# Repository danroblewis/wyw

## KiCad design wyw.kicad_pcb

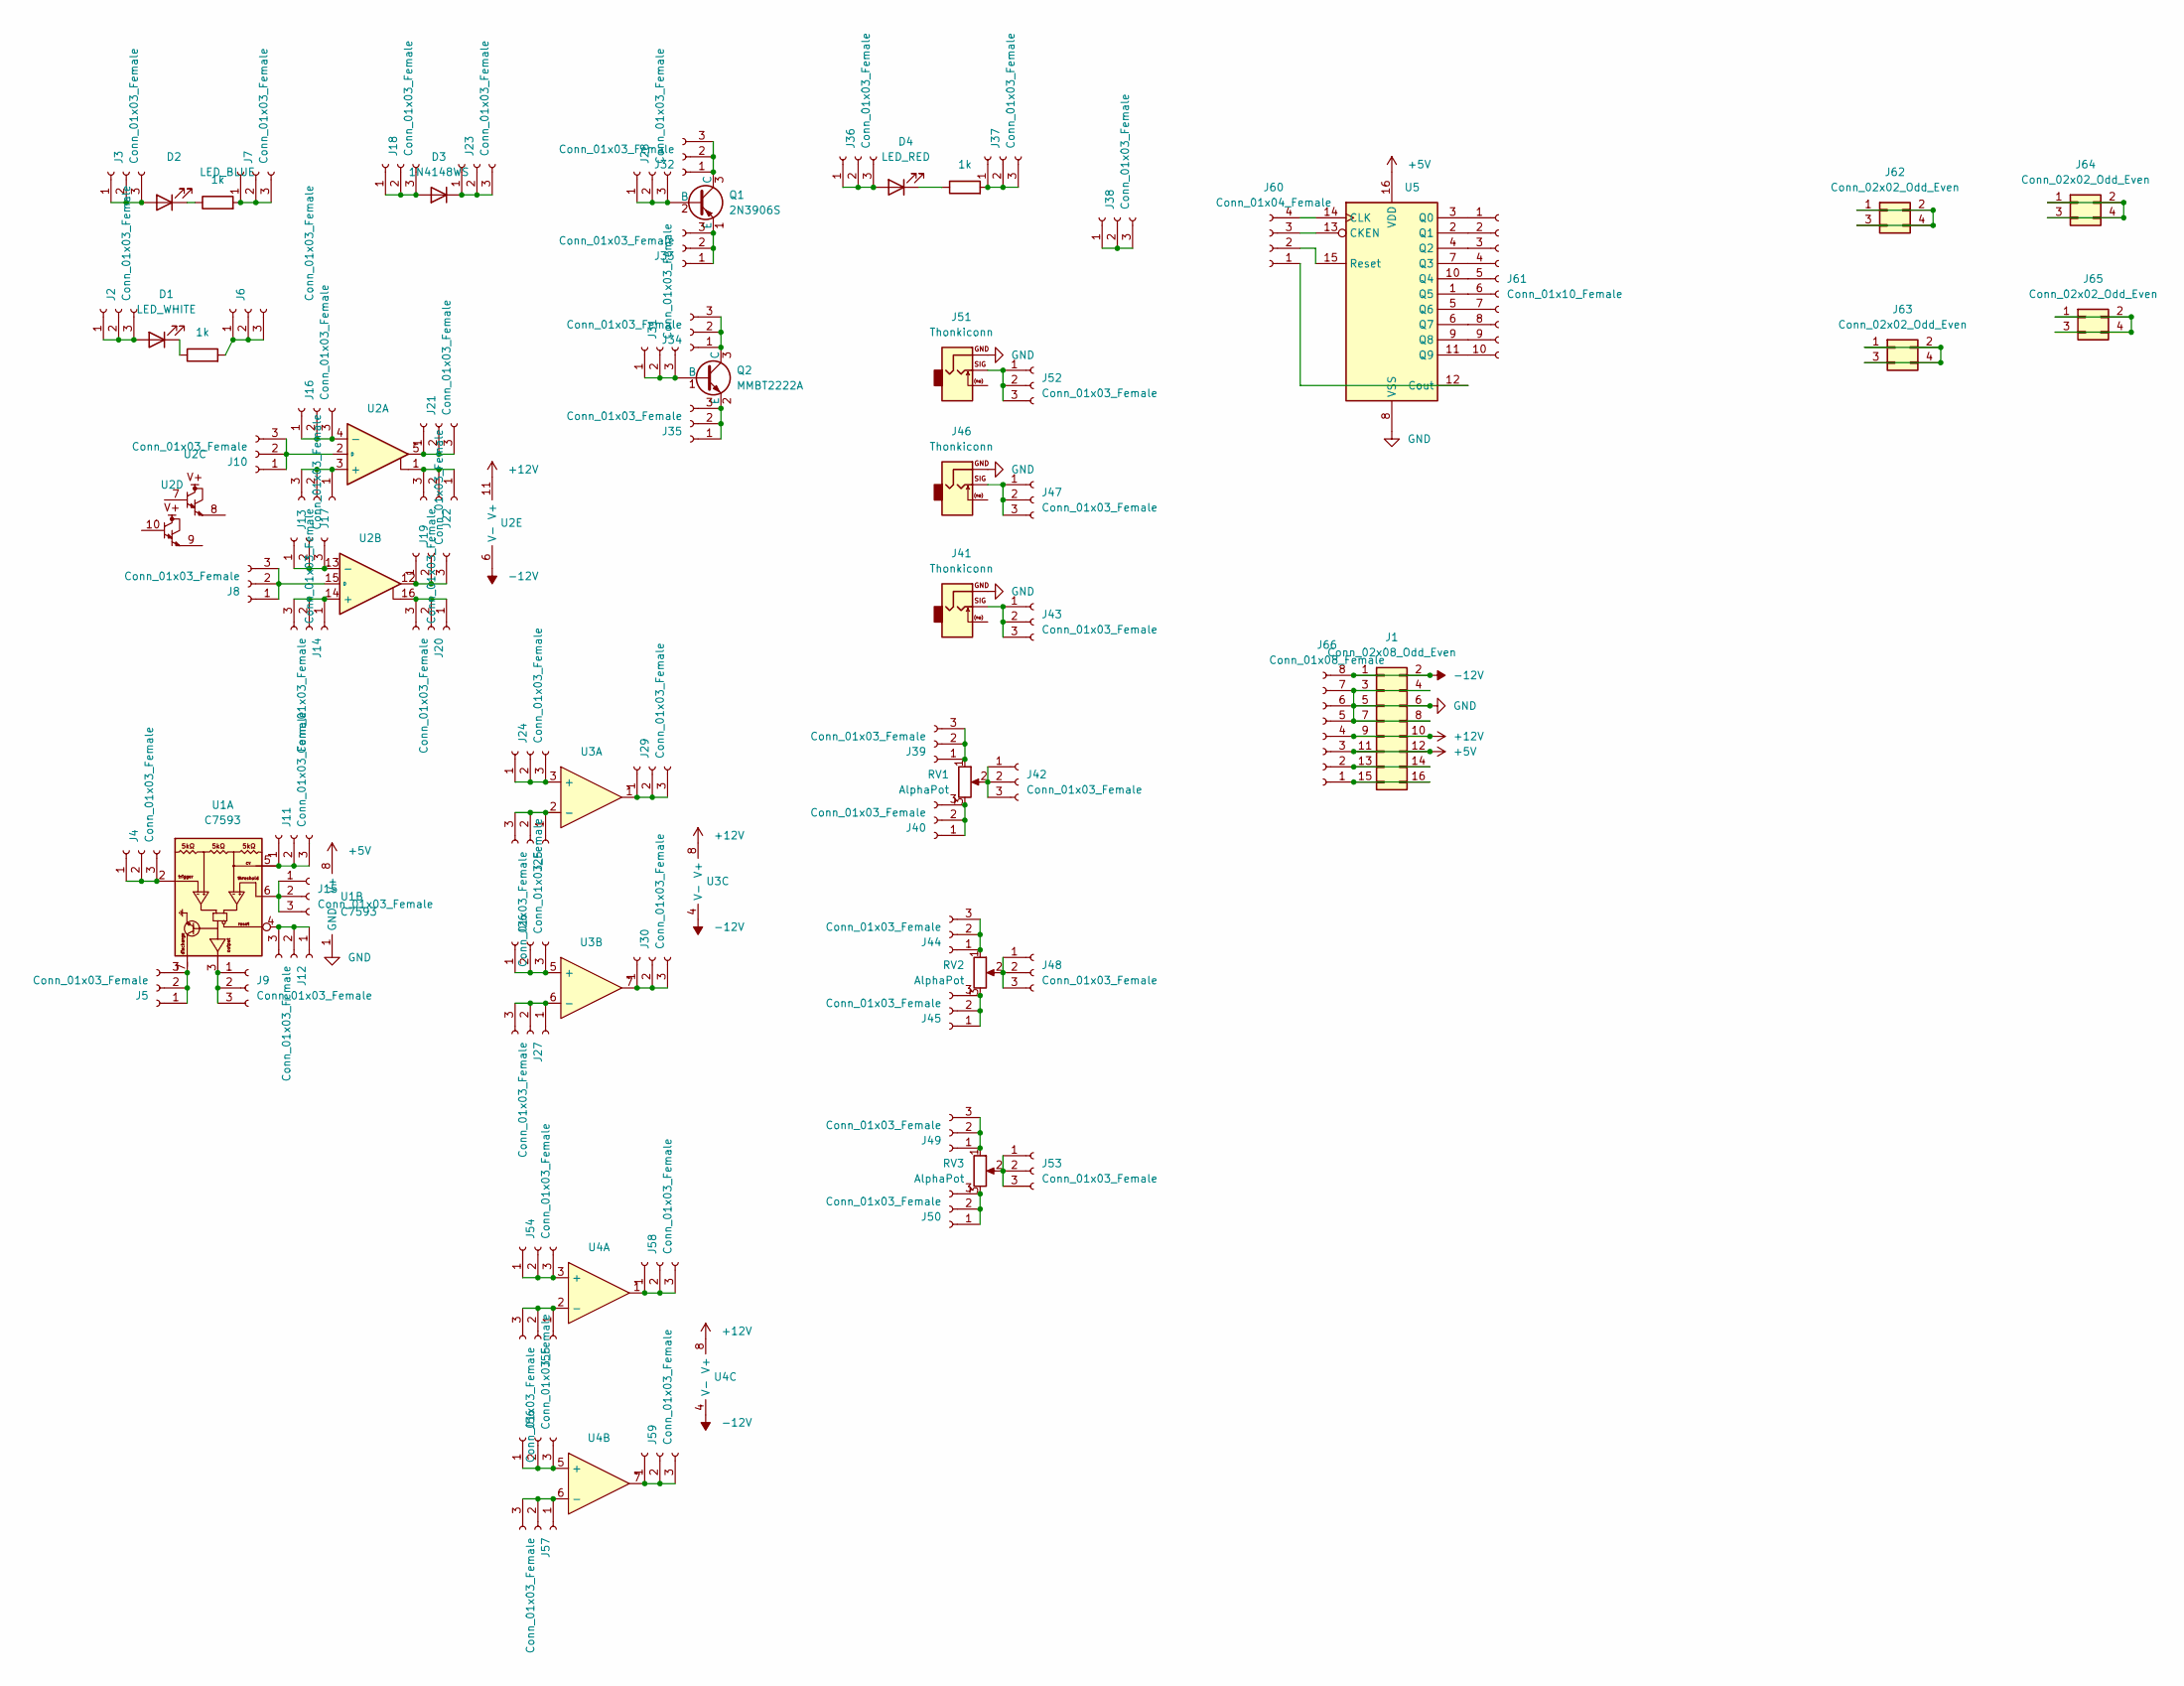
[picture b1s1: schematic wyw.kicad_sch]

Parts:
D1: LED_WHITE; LED_0603_1608Metric; LCSC C2290
D2: LED_BLUE; LED_0603_1608Metric; LCSC C72041
D3: 1N4148WS; D_SOD-323; LCSC C2128
D4: LED_RED; LED_0603_1608Metric; LCSC C2296
J1: Conn_02x08_Odd_Even; IDC-Header_2x08_P2.54mm_Vertical
J2, J3, J4, J5, J6, J7, J8, J9, J10, J11, J12, J13, J14, J15, J16, J17, J18, J19, J20, J21, J22, J23, J24, J25, J26, J27, J28, J29, J30, J31, J32, J33, J34, J35, J36, J37, J38, J39, J40, J42, J43, J44, J45, J47, J48, J49, J50, J52, J53, J54, J55, J56, J57, J58, J59: Conn_01x03_Female; PinHeader_1x03_P2.54mm_Vertical
J41, J46, J51: Thonkiconn; Jack_3.5mm_QingPu_WQP-PJ398SM_Vertical_CircularHoles
J60: Conn_01x04_Female; PinHeader_1x04_P2.54mm_Vertical
J61: Conn_01x10_Female; PinHeader_1x10_P2.54mm_Vertical
J62, J63, J64, J65: Conn_02x02_Odd_Even; PinHeader_2x02_P2.54mm_Vertical
J66: Conn_01x08_Female; PinHeader_1x08_P2.54mm_Vertical
Q1: 2N3906S; SOT-23-3; LCSC C147294
Q2: MMBT2222A; SOT-23-3; LCSC C8512
R1, R2, R4: 1k; R_0603_1608Metric; LCSC C21190
RV1, RV2, RV3: AlphaPot; Potentiometer_Alpha_RD901F-40-00D_Single_Vertical
U1: NE555DR; SOIC-8-1EP_3.9x4.9mm_P1.27mm_EP2.29x3mm; LCSC C7593
U2: LM13700; SOIC-16_3.9x9.9mm_P1.27mm; LCSC C174050
U3, U4: TL072; SOIC-8_3.9x4.9mm_P1.27mm; LCSC C6961
U5: 4017bm; SOP-16_3.9x9.9mm_P1.27mm; LCSC C356694

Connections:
+5V: J1.11, J1.12, J66.3, U1.8 (V+), U5.16 (VDD)
+12V: J1.9, J1.10, J66.4, U2.11 (V+), U3.8 (V+), U4.8 (V+)
-12V: J1.1, J1.2, J66.8, U2.6 (V-), U3.4 (V-), U4.4 (V-)
GND: J1.3, J1.4, J1.5, J1.6, J1.7, J1.8, J41.S, J46.S, J51.S, J66.5, J66.6, J66.7, U1.1 (GND), U5.8 (VSS)
unnamed: D1.1 (K), R1.1
unnamed: D1.2 (A), J2.1, J2.2, J2.3
unnamed: D2.1 (K), R2.1
unnamed: D2.2 (A), J3.1, J3.2, J3.3
unnamed: D3.1 (K), J23.1, J23.2, J23.3
unnamed: D3.2 (A), J18.1, J18.2, J18.3
unnamed: D4.1 (K), R4.1
unnamed: D4.2 (A), J36.1, J36.2, J36.3
unnamed: J1.13, J1.14, J66.2
unnamed: J1.15, J1.16, J66.1
unnamed: J4.1, J4.2, J4.3, U1.2
unnamed: J5.1, J5.2, J5.3, U1.7
unnamed: J6.1, J6.2, J6.3, R1.2
unnamed: J7.1, J7.2, J7.3, R2.2
unnamed: J8.1, J8.2, J8.3, U2.15 (D)
unnamed: J9.1, J9.2, J9.3, U1.3
unnamed: J10.1, J10.2, J10.3, U2.2 (D)
unnamed: J11.1, J11.2, J11.3, U1.5
unnamed: J12.1, J12.2, J12.3, U1.4
unnamed: J13.1, J13.2, J13.3, U2.13 (-)
unnamed: J14.1, J14.2, J14.3, U2.14 (+)
unnamed: J15.1, J15.2, J15.3, U1.6
unnamed: J16.1, J16.2, J16.3, U2.4 (-)
unnamed: J17.1, J17.2, J17.3, U2.3 (+)
unnamed: J19.1, J19.2, J19.3, U2.12
unnamed: J20.1, J20.2, J20.3, U2.16
unnamed: J21.1, J21.2, J21.3, U2.5
unnamed: J22.1, J22.2, J22.3, U2.1
unnamed: J24.1, J24.2, J24.3, U3.3 (+)
unnamed: J25.1, J25.2, J25.3, U3.2 (-)
unnamed: J26.1, J26.2, J26.3, U3.5 (+)
unnamed: J27.1, J27.2, J27.3, U3.6 (-)
unnamed: J28.1, J28.2, J28.3, Q1.2 (B)
unnamed: J29.1, J29.2, J29.3, U3.1
unnamed: J30.1, J30.2, J30.3, U3.7
unnamed: J31.1, J31.2, J31.3, Q2.1 (B)
unnamed: J32.1, J32.2, J32.3, Q1.3 (C)
unnamed: J33.1, J33.2, J33.3, Q1.1 (E)
unnamed: J34.1, J34.2, J34.3, Q2.3 (C)
unnamed: J35.1, J35.2, J35.3, Q2.2 (E)
unnamed: J37.1, J37.2, J37.3, R4.2
unnamed: J38.1, J38.2, J38.3
unnamed: J39.1, J39.2, J39.3, RV1.1
unnamed: J40.1, J40.2, J40.3, RV1.3
unnamed: J41.T, J43.1, J43.2, J43.3
unnamed: J42.1, J42.2, J42.3, RV1.2
unnamed: J44.1, J44.2, J44.3, RV2.1
unnamed: J45.1, J45.2, J45.3, RV2.3
unnamed: J46.T, J47.1, J47.2, J47.3
unnamed: J48.1, J48.2, J48.3, RV2.2
unnamed: J49.1, J49.2, J49.3, RV3.1
unnamed: J50.1, J50.2, J50.3, RV3.3
unnamed: J51.T, J52.1, J52.2, J52.3
unnamed: J53.1, J53.2, J53.3, RV3.2
unnamed: J54.1, J54.2, J54.3, U4.3 (+)
unnamed: J55.1, J55.2, J55.3, U4.2 (-)
unnamed: J56.1, J56.2, J56.3, U4.5 (+)
unnamed: J57.1, J57.2, J57.3, U4.6 (-)
unnamed: J58.1, J58.2, J58.3, U4.1
unnamed: J59.1, J59.2, J59.3, U4.7
unnamed: J60.1, U5.12 (Cout)
unnamed: J60.2, U5.15 (Reset)
unnamed: J60.3, U5.13 (CKEN)
unnamed: J60.4, U5.14 (CLK)
unnamed: J61.1, U5.3 (Q0)
unnamed: J61.2, U5.2 (Q1)
unnamed: J61.3, U5.4 (Q2)
unnamed: J61.4, U5.7 (Q3)
unnamed: J61.5, U5.10 (Q4)
unnamed: J61.6, U5.1 (Q5)
unnamed: J61.7, U5.5 (Q6)
unnamed: J61.8, U5.6 (Q7)
unnamed: J61.9, U5.9 (Q8)
unnamed: J61.10, U5.11 (Q9)
unnamed: J62.1, J62.2, J62.3, J62.4
unnamed: J63.1, J63.2, J63.3, J63.4
unnamed: J64.1, J64.2, J64.3, J64.4
unnamed: J65.1, J65.2, J65.3, J65.4

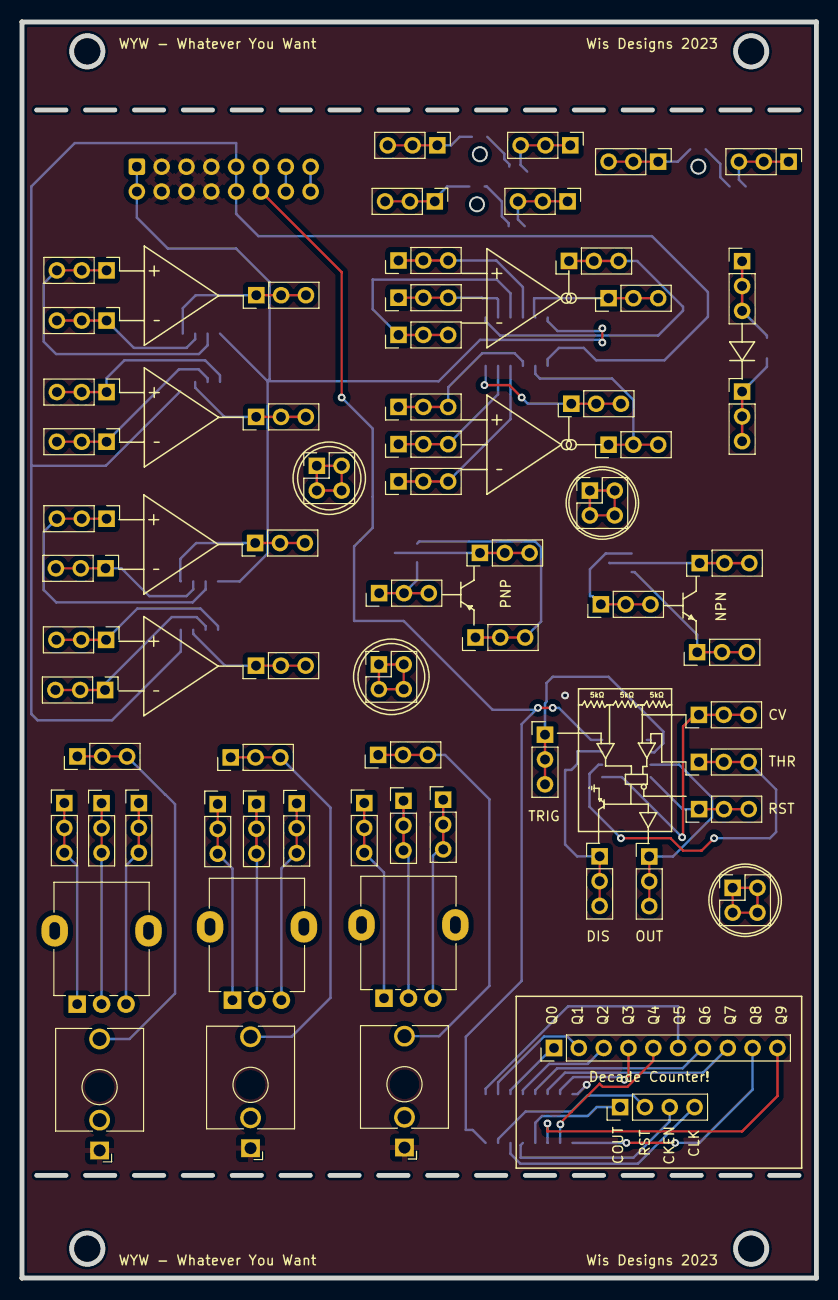
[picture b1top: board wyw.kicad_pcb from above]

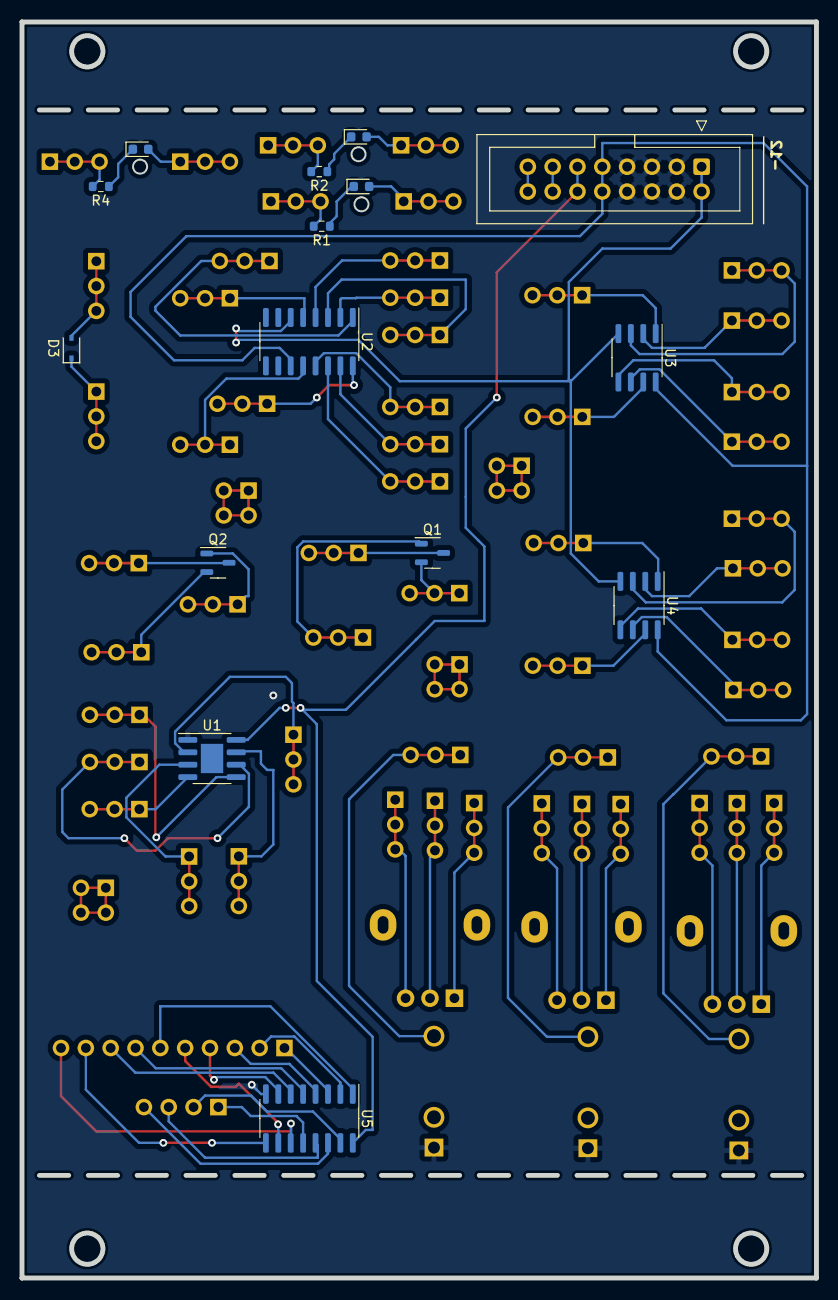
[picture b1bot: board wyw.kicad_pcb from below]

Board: 2 copper layers, 81.3 x 128.5 mm, 81 parts (15 on the bottom side), 81 nets.

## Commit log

2023-02-18 asdf
